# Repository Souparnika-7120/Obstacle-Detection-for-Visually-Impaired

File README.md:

# Obstacle-Detection-for-Visually-Impaired
# Obstacle Detection System for Visually Impaired Person using ESP32

## 📌 Overview

This project is an assistive system designed to help visually impaired individuals detect obstacles in their path. It uses an ultrasonic sensor to measure distance and alerts the user using a buzzer when an object is nearby.

---

## 🎯 Objective

To develop a simple, low-cost, and reliable obstacle detection system that enhances the safety and mobility of visually impaired people.

---

## 🚀 Features

* Real-time obstacle detection
* Audio alert using buzzer
* Compact and portable design
* Low-cost implementation
* Custom PCB designed using EAGLE

---

## 🛠️ Components Used

* ESP32 Development Board
* Ultrasonic Sensor (HC-SR04)
* Buzzer
* Power Supply (5V)
* Custom PCB

---

## ⚙️ Working Principle

The ultrasonic sensor sends ultrasonic waves and receives the reflected signal to calculate distance.

* If distance > 20 cm → No alert
* If distance ≤ 20 cm → Buzzer turns ON

This helps the user identify nearby obstacles.

---

## 🔌 Circuit Connections

| Component | ESP32 Pin |
| --------- | --------- |
| Trigger   | GPIO 32   |
| Echo      | GPIO 33   |
| Buzzer    | GPIO 27   |
| VCC       | 5V (VIN)  |
| GND       | GND       |

---

## 💻 Code

The Arduino code for this project is available in the `code/` folder.

---

## 🧩 PCB Design

* Designed using Autodesk EAGLE
* Includes schematic and PCB layout
* Gerber files provided for fabrication
* Ground plane implemented for better performance

---

## 📂 Project Structure

```
Obstacle-Detection-for-Visually-Impaired/
│
├── code/              # Arduino code
├── pcb_design/        # PCB files (EAGLE + Gerber)
├── images/            # Project images
├── docs/              # Report/documentation
└── README.md
```

---

## 📷 Project Images

The images of the project is there under the imagr folder 

[PCB Layout](images/pcb_layout.png)

---

## 🧪 Results

The system successfully detects obstacles within a predefined range and alerts the user using a buzzer.

---

## 🔮 Future Enhancements

* Add vibration motor for silent alerts
* Integrate GPS tracking system
* Add GSM module for emergency alerts
* AI-based object detection

---

## 👩‍💻 Author

S SOUPARNIKA
B.Tech ECE (AI & Cybernetics)

---

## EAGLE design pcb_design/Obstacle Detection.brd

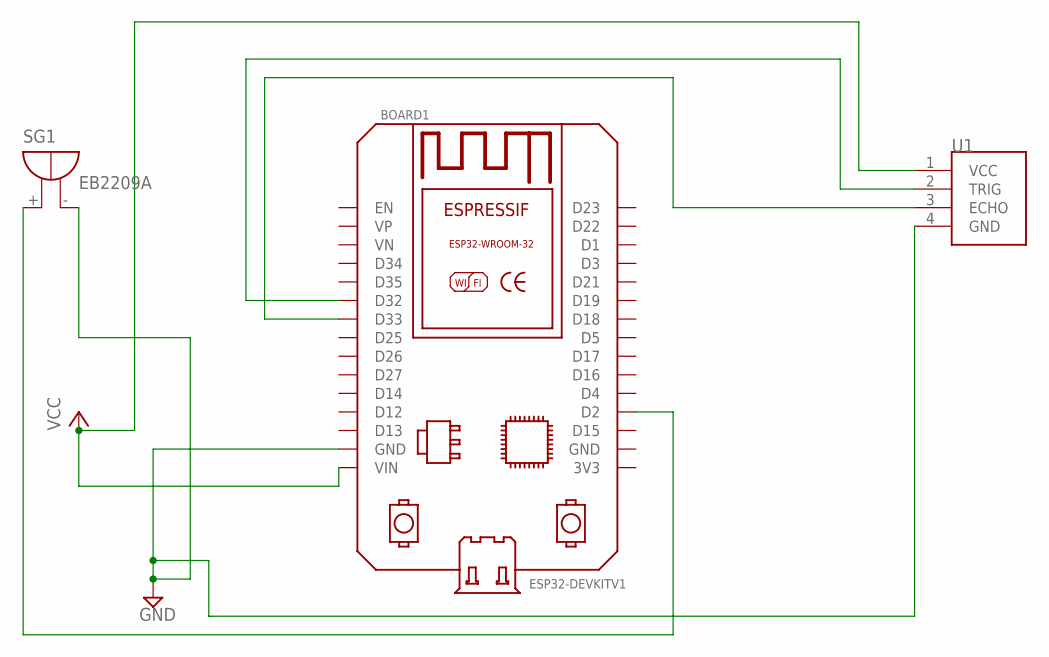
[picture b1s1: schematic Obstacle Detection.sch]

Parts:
BOARD1: ESP32DEVKITV1; ESP32-DEVKITV1
SG1: EB2209A
U1: HC-SR04; XCVR_HC-SR04

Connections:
GND: BOARD1.GND, SG1.-, U1.4 (GND)
unnamed: BOARD1.D32, U1.2 (TRIG)
unnamed: BOARD1.D33, U1.3 (ECHO)
unnamed: BOARD1.D2, SG1.+
VCC: BOARD1.VIN, U1.1 (VCC)

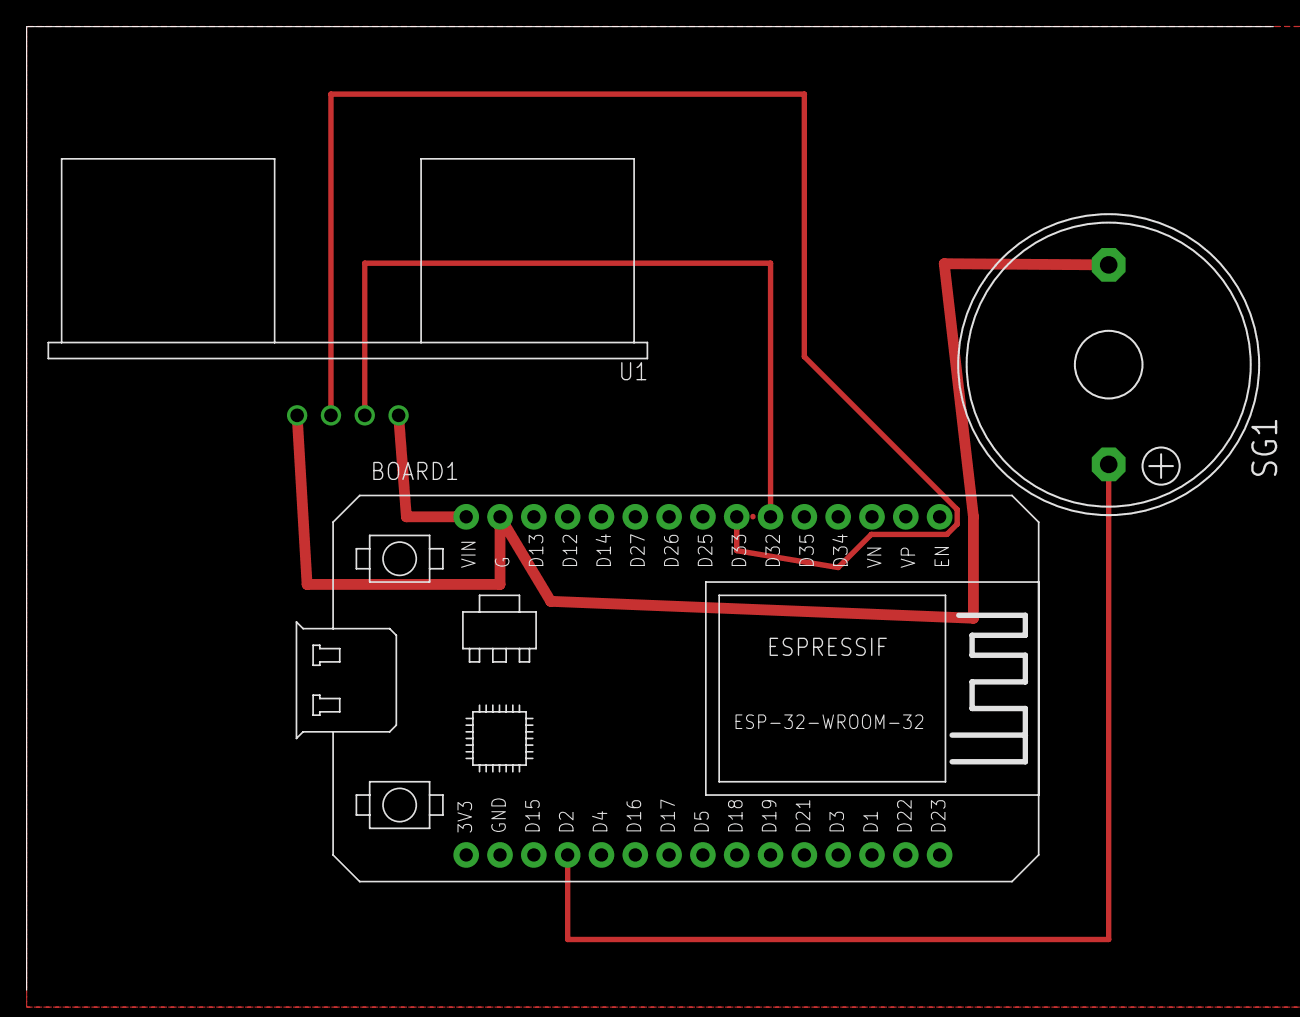
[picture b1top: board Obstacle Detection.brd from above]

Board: 2 copper layers, 93.7 x 72.4 mm, 3 parts (0 on the bottom side), 5 nets.

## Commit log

2026-05-04 LICENSE
